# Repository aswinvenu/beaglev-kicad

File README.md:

# BeagleV-Kicad

BeagleV Kicad project files

Convert BeagleV design files from OrCad and Allegro to its equivalent Kicad files.

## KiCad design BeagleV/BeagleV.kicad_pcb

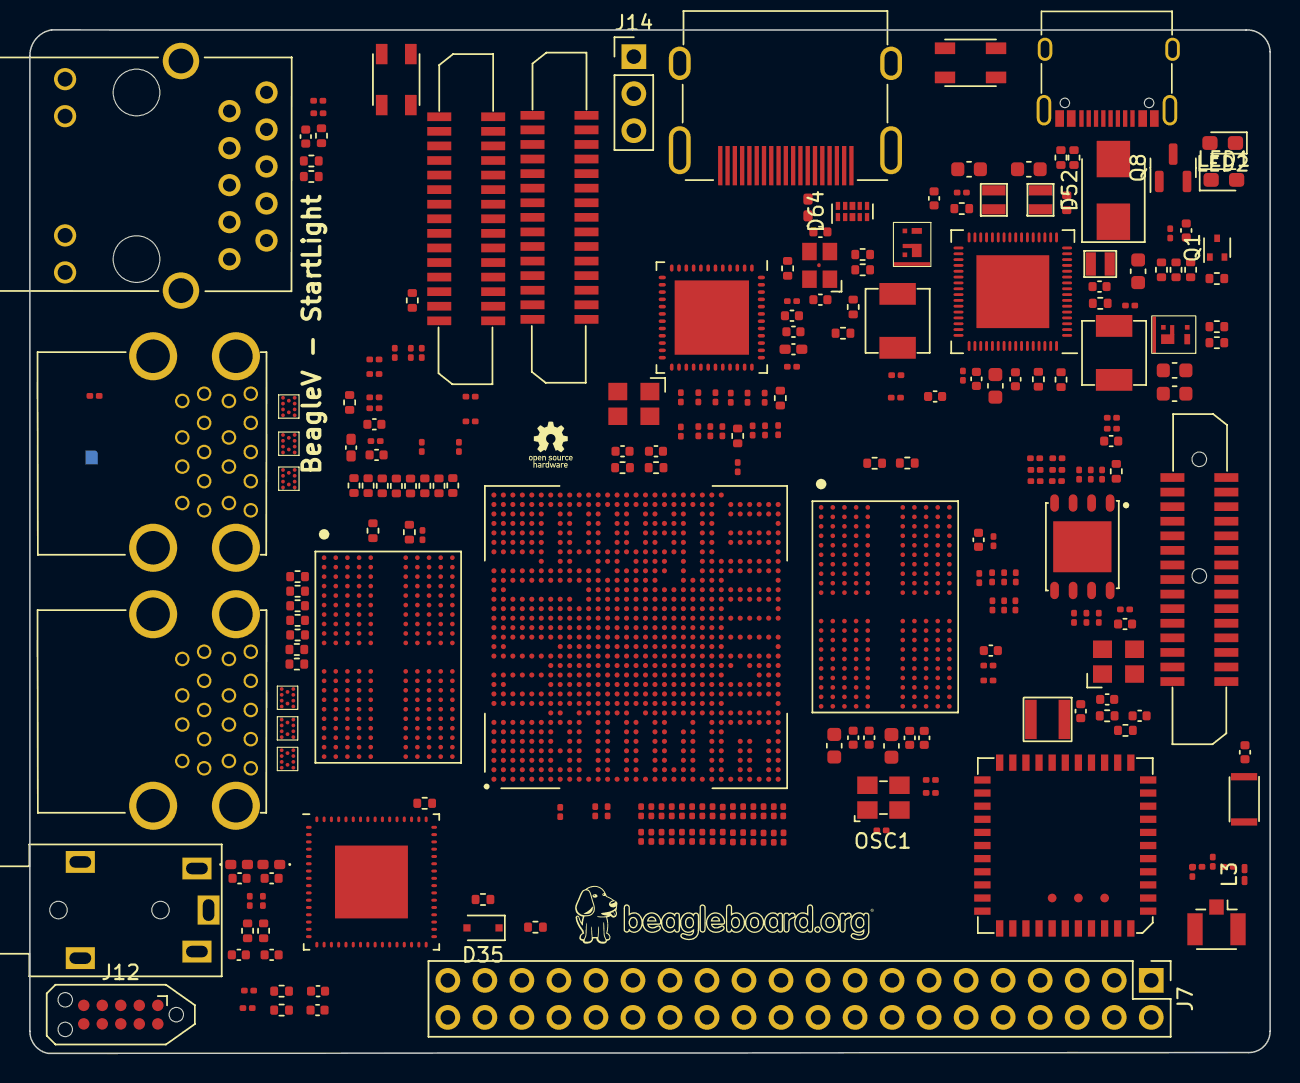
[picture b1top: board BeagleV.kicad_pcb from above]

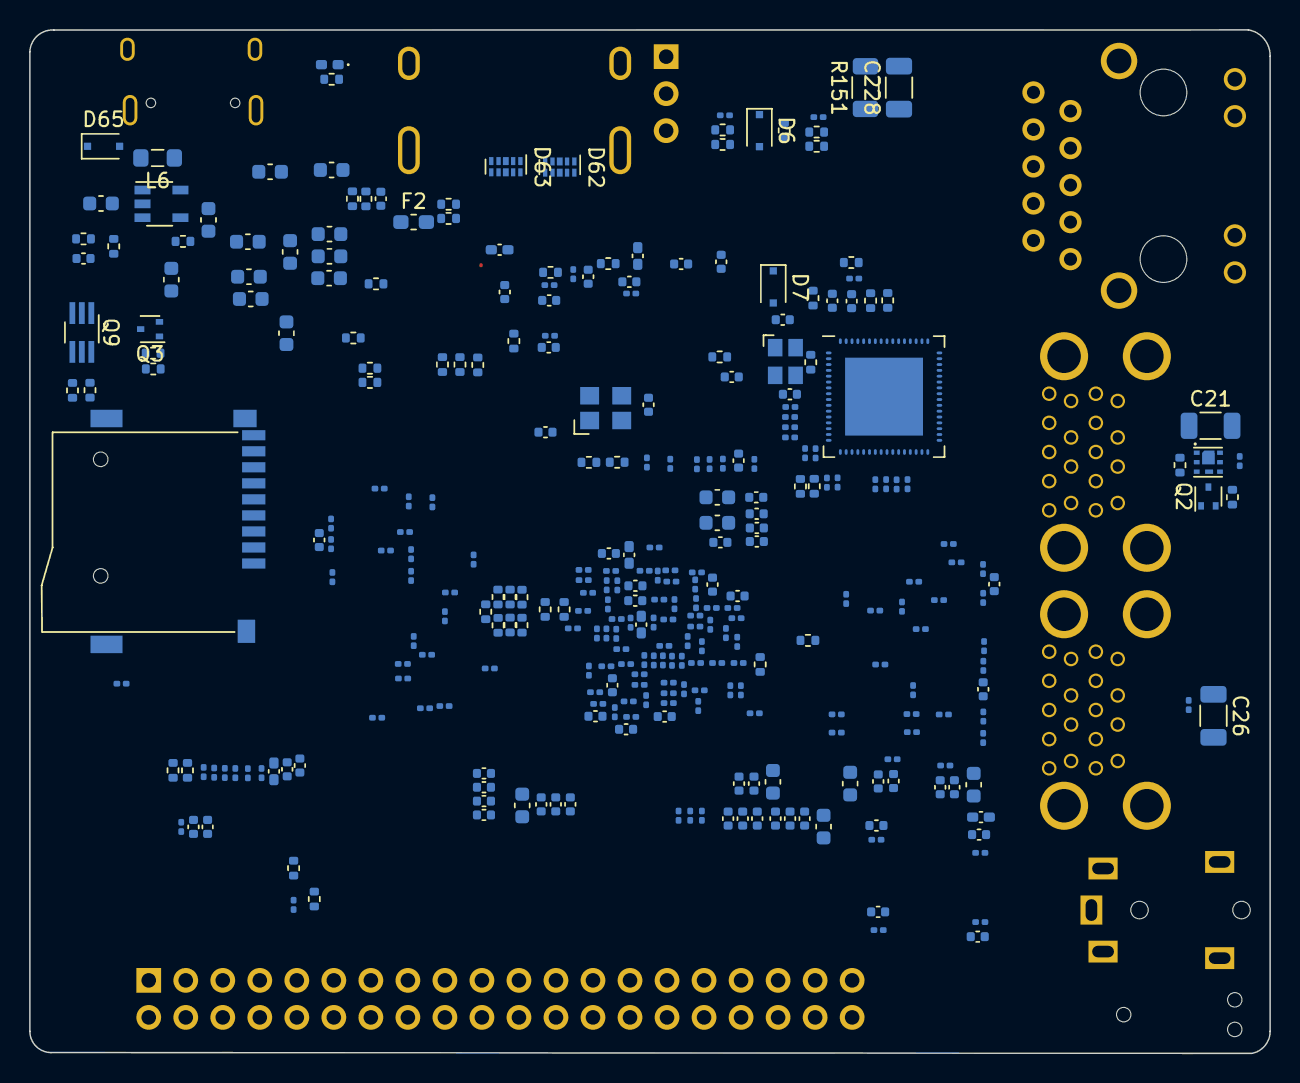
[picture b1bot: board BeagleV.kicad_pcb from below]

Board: 12 copper layers, 85.1 x 70.2 mm, 574 parts (315 on the bottom side), 536 nets.

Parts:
ANT1: RFECA3216060A1T
C1, C5, C6, C7, C8, C9, C11, C12, C13, C14, C15, C16, C17, C18, C19, C20, C24, C25, C29, C33, C35, C37, C39, C50, C51, C52, C53, C54, C55, C56, C57, C58, C61, C62, C63, C64, C65, C66, C70, C71, C72, C73, C74, C75, C76, C77, C78, C82, C83, C84, C85, C86, C87, C88, C89, C90, C93, C94, C95, C96, C97, C98, C102, C103, C104, C105, C106, C107, C108, C109, C110, C112, C113, C114, C115, C117, C118, C119, C124, C125, C126, C127, C128, C129, C130, C131, C132, C137, C138, C139, C140, C146, C147, C148, C149, C150, C151, C152, C153, C154, C161, C162, C163, C164, C165, C166, C167, C168, C169, C170, C171, C172, C173, C174, C175, C179, C180, C181, C183, C184, C185, C186, C189, C190, C191, C193, C194, C195, C199, C201, C203, C205, C207, C209, C210, C211, C212, C217, C219, C221, C229, C237, C238, C239, C240, C241, C242, C243, C244, C245, C267, C269, C270, C272, C277, C279, C281, C282, C286, C287, C297, C300: 100nF/10V; C_0201_0603Metric
C2: 100nF/10V1; C_0201_0603Metric
C3: 100n/10V; C_0201_0603Metric
C4, C10, C22, C23, C28, C32, C34, C36, C38, C91, C92, C99, C111, C177, C230, C231, C232, C278, C280: 10uF/6.3V; C_0402_1005Metric
C21: 100uF/6.3V; C_1206_3216Metric
C26: 100uF/10V; C_1206_3216Metric
C27, C68, C80, C100, C120, C134, C142, C156, C157, C248, C273, C274, C275, C276, C283, C284, C294, C295: 22uF/10V; C_0603_1608Metric
C30, C31: 100uF/4V; C_0402_1005Metric
C40, C227, C311, C312, C313, C314: 10nF/50V; C_0402_1005Metric
C42, C44: DNP; C_0402_1005Metric
C43, C45, C235, C236: 22pF/50V; C_0402_1005Metric
C46, C215, C223, C224: 10pF; C_0402_1005Metric
C47, C233, C250: 100nF/10V; C_0402_1005Metric
C48: 22uF; C_0603_1608Metric
C49, C69, C81, C101, C116, C123, C136, C145, C160, C178, C182, C188, C192, C198, C202, C204, C206, C208, C216, C218, C220, C234, C309, C310: 1uF/10V; C_0402_1005Metric
C59, C60, C67, C187: 10uF/6.4V; C_0402_1005Metric
C79: 10uf/6.4V; C_0402_1005Metric
C121, C122, C135, C143, C158, C159, C288, C298: 10uF/10V; C_0402_1005Metric
C133, C141, C155, C176: 1nF/10V; C_0402_1005Metric
C144: 0uF/10V; C_0402_1005Metric
C196, C226: DNP; C_0201_0603Metric
C197: 100nF; C_0402_1005Metric
C200, C266, C271: 2.2uF/6.3V; C_0402_1005Metric
C213: 1pF/50V; C_0201_0603Metric
C222, C306, C307: 4.7uF/10V; C_0402_1005Metric
C228: 1nF/2kV; C_1206_3216Metric
C246, C247: 22pF; C_0402_1005Metric
C249, C291, C293, C304: 10uF/10V; C_0603_1608Metric
C268, C296: 2.2uF/10V; C_0402_1005Metric
C289, C290, C308: 2.2uF/10V; C_0603_1608Metric
C301: 2.2uF; C_0603_1608Metric
C302: 1nF/50V; C_0402_1005Metric
C303: 10uF; C_0603_1608Metric
C305: 100nF; C_0201_0603Metric
D1, D2, D4: D_TVS; D_0402_1005Metric_Pad0.77x0.64mm_HandSolder
D5: ESDPSA0402V05; D_0402_1005Metric_Pad0.77x0.64mm_HandSolder
D6, D7, D35, D65: PMEG3010CEJ; D_SOD-323F
D27, D28, D29, D30, D31, D32: PCMF2USB3S
D52: SMBJ5.0CA-TR; D_SMB
D62, D63, D64: Protection-Diode; USON-10_2.5x1.0mm_P0.5mm
F2: Fuse; Fuse_0603_1608Metric_Pad1.05x0.95mm_HandSolder
FB1, FB2, FB3, FB6: FerriteBead; L_0402_1005Metric_Pad0.77x0.64mm_HandSolder
FB4, FB7, FB8, FB9: FerriteBead 120R; L_0402_1005Metric_Pad0.77x0.64mm_HandSolder
J1, J2, J9: FPC_CONN_2X15P; FPC-1-1734248-5
J3: audio_5p_mj2135_5d6_14_7x7x6mm; PJ322
J4, J5: USB-TYPE-A-3.0; Stacked-USB-TypeA
J6: LPJG0801HBNL; LPJG0801EBNL
J7: PI-Connector-2x20-2.54mm; PinHeader_2x20_P2.54mm_Vertical
J8: U.FL-R-SMT-1
J10: MICRO_SD_ST_TF_003A_16_1x14_5mm; ST-TF-003A
J11: ST-HD-010; HDMI-Type-A
J12: JTAG-Connector; Tag-Connect_TC2050-IDC-NL_2x05_P1.27mm_Vertical
J13: USB_TYPE_C; USB-Type-C
J14: DNP Conn_01x03_Male; PinHeader_1x03_P2.54mm_Vertical
L1, L7, L8: 1uH; WPN201610H_2x1.6
L2: 3.3uH; Sunlord_3.0x3.0
L3: 10nH; L_0201_0603Metric_Pad0.64x0.40mm_HandSolder
L4: 0.47uH; Codaca_4.4x4.4
L5: 0.56uH; Codaca_4.4x4.4
L6: 10uH; L_0805_2012Metric_Pad1.05x1.20mm_HandSolder
LED1: GREEN LED; LED_0603_1608Metric_Pad1.05x0.95mm_HandSolder
LED2: RED LED; LED_0603_1608Metric_Pad1.05x0.95mm_HandSolder
OSC1: 32.768kHz-clock; 7XZ-32.768KHz
Q1, Q2, Q3: CJ1012; SOT-523
Q6, Q7: CSD87381P
Q8: IRLML6401; SOT-23
Q9: BCM857BS-7F-F; SOT-363_SC-70-6_Handsoldering
R1, R28, R29, R30, R31, R32, R33, R34, R123, R124, R125, R126, R134, R137, R147, R148, R149, R150, R152, R153: 10K; R_0201_0603Metric
R2, R3, R35, R38, R55, R56, R84, R85, R117, R161: 1K; R_0402_1005Metric
R4, R101, R127, R128, R129, R131, R167: 4.7K; R_0402_1005Metric
R5, R6, R7, R8, R9, R10, R11, R12, R13, R14, R15, R16, R17, R18, R19, R20, R21, R22, R41, R42, R43, R44, R45, R46, R47, R48, R49, R50, R51, R52, R53, R54, R87, R88, R89, R90, R91, R92, R93, R94, R102, R103, R104, R105, R106, R107, R108, R109, R110, R113, R114, R145, R156, R157, R158, R232, R233, R234, R235, R236, R237, R238, R265, R266, R267, R268: 33R; R_0201_0603Metric
R23: 680R; R_0402_1005Metric
R24, R86: 27K; R_0402_1005Metric
R25, R26, R144, R146, R160: 100K; R_0402_1005Metric
R27, R37, R58, R59, R63, R67, R76, R116, R119, R121, R122, R140, R155, R165, R166, R254, R255, R257, R259, R260: 0R; R_0402_1005Metric
R36, R39: 1K; R_0201_0603Metric
R57, R115, R120, R143, R263: 1M; R_0402_1005Metric
R60: 12K; R_0402_1005Metric
R61, R65, R66, R69, R70, R74, R75, R78, R79, R95, R96, R97, R98, R136, R139, R154, R164, R240, R242, R244, R247: DNP; R_0402_1005Metric
R62, R71, R72, R80, R81, R184: 240R; R_0402_1005Metric
R64, R68, R73, R77, R82, R83, R99, R100, R111, R112, R118, R138, R142, R241, R243, R245, R246, R252: 10K; R_0402_1005Metric
R130, R135, R141: DNP; R_0201_0603Metric
R133: 0R; R_0201_0603Metric
R151: 1M; R_1206_3216Metric
R159: 10k; R_0402_1005Metric
R162, R163, R261: 49.9K; R_0402_1005Metric
R248, R249: 5.1K; R_0402_1005Metric
R256, R262: 12.1K; R_0402_1005Metric
R258: 2.2K; R_0402_1005Metric
R264: 13.3K; R_0402_1005Metric
R269, R270, R271, R272: 120R; R_0402_1005Metric
SW2, SW3: Tactile-Switch; switch
U1: GL3520-OS322; GL3520-22-QFN-64_EP_8x8_Pitch0.4mm
U2: ETA6020D2G; ETA6020-DFN2x2-6L
U5: KSZ9031RNXCA; KSZ9031RNX-QFN-48_EP_7.3x7.3_Pitch0.5mm
U7, U8: 32Gbit_RAM; LPDDR4-200-WFBGA-10x14.5
U9: VIC-V10; JH7100 - BGA-961_31x31_20.5x20.5mm
U11: TDA19988; TDA19988-QFN-64_EP_9x9_Pitch0.5mm
U12: AP6236
U13: LMR62014; DBV0005A-SOT-23
U14: TPS65086100; TPS650861-QFN-64_EP_8.15x8.15_Pitch0.4mm
U16: GD25LQ256DWIGR; GD25LQ256D
X1: 25MHz; SMCE-2520
X2: 25MHz; SMCE-3225
X3: 27MHz; SMCE-3225
X4: Crystal; SMCE-3225
X6: 25MHz - Crystal; SMCE-2520

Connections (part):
3V3_WIFI: C3.1, C229.1, C230.1, C231.1, C233.1, C234.1, FB9.2, OSC1.1 (EN), OSC1.4 (VDD), R130.1, R137.2, R141.1, U12.9 (VBAT), U12.22 (VDDIO)
+1V1: C48.1, C49.1, C50.1, C51.1, C52.1, C53.1, C54.1, C55.1, C56.1, C57.1, C58.1, C59.1, C68.1, C69.1, C70.1, C71.1, C72.1, C73.1, C74.1, C75.1, C76.1, C77.1, C78.1, C79.1, C80.1, C81.1, C82.1, C83.1, C84.1, C85.1, C86.1, C87.1, C88.1, C89.1, C90.1, C91.1, C100.1, C101.1, C102.1, C103.1, C104.1, C105.1, C106.1, C107.1, C108.1, C109.1, C110.1, C111.1, C120.1, C121.1, C122.1, C123.1, C124.1, C125.1, C126.1, C127.1, C128.1, C129.1, C130.1, C131.1, C132.1, C133.1, C142.1, C143.1, C144.1, C145.1, C146.1, C147.1, C148.1, C149.1, C150.1, C151.1, C152.1, C153.1, C154.1, C155.1, C282.2, C297.2, C298.2, L5.2, R62.1, R64.1, R70.1, R71.1, R72.1, R73.1, R79.1, R82.1, R83.1, R184.1, U8.A4 (VDD2_00), U8.A9 (VDD2_1), U8.AB4 (VDD2_22), U8.AB9 (VDD2_23), U8.F5 (VDD2_2), U8.F8 (VDD2_3), U8.H1 (VDD2_4), U8.H5 (VDD2_5), U8.H8 (VDD2_6), U8.H12 (VDD2_7), U8.K1 (VDD2_8), U8.K3 (VDD2_9), U8.K10 (VDD2_10), U8.K12 (VDD2_11), U8.N1 (VDD2_12)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
+1V2: C10.1, C16.1, C17.1, C18.1, C27.2, C30.1, C248.2, FB2.1, FB3.1, FB4.1, L1.2, R37.1, U1.39 (DVDD12), U1.56 (DVDD12_1), U1.62 (DVDD12_2), U14.22 (FB5)
+1V8: C60.1, C61.1, C62.1, C63.1, C64.1, C65.1, C66.1, C67.1, C92.1, C93.1, C94.1, C95.1, C96.1, C97.1, C98.1, C99.1, C134.1, C135.1, C136.1, C137.1, C138.1, C139.1, C140.1, C141.1, C198.1, C199.1, C202.1, C203.1, C206.1, C207.1, C210.1, C211.1, C212.1, C216.1, C217.1, C275.2, C276.2, C296.2, FB6.2, J12.1, L8.2, R98.1, R99.2, R101.2, R161.1, R240.1, R242.1, R244.1, R246.1, SW3.1, SW3.3, U7.F1 (VDD1_00), U7.F12 (VDD1_1), U7.G4 (VDD1_2), U7.G9 (VDD1_3), U7.T4 (VDD1_4), U7.T9 (VDD1_5), U7.U1 (VDD1_6), U7.U12 (VDD1_7), U8.F1 (VDD1_00), U8.F12 (VDD1_1), U8.G4 (VDD1_2), U8.G9 (VDD1_3), U8.T4 (VDD1_4), U8.T9 (VDD1_5), U8.U1 (VDD1_6), U8.U12 (VDD1_7), U9.AB21 (DVDD18_OTP), U9.AD24 (AVDD18_USB), U9.M8 (VDD18_00), U9.M9 (VDD18_01), U9.M23 (AVDD18_MIPITX), U9.N8 (VDD18_02), U9.N9 (VDD18_03), U9.N10 (VDD18_04), U9.N11 (VDD18_05), U9.P8 (VDD18_06), U9.P9 (VDD18_07), U9.P10 (VDD18_08), U9.P11 (VDD18_09), U9.R8 (VDD18_10), U9.R9 (VDD18_11), U9.R10 (VDD18_12), U9.R11 (VDD18_13), U9.T23 (AVDD18_MIPIRX), U9.W23 (AVDD18_TS), U14.23 (FB4), U14.32 (PVINSWA1), U16.8 (VCC)
+3V3: C1.1, C2.1, C177.1, C178.1, C179.1, C180.1, C181.1, C182.1, C183.1, C184.1, C187.1, C188.1, C189.1, C190.1, C191.1, C192.1, C193.1, C194.1, C195.1, C272.1, C273.2, C274.2, C278.1, C279.1, FB1.1, FB8.1, FB9.1, J1.15, J2.15, J7.1, J7.17, J9.14, J9.15, J10.4 (VDD), L7.2, R1.2, R27.1, R86.1, R100.1, R112.2, R123.2, R124.2, R125.2, R126.2, R127.1, R128.1, R129.1, R131.1, R134.2, R147.2, R160.1, U9.AA9 (VDD3318_SENSOR_00), U9.AA21 (VDD3318_GMII_1), U9.AB9 (VDD3318_SENSOR_1), U9.N13 (VDD3318_CHIPLINK_00), U9.N14 (VDD3318_CHIPLINK_1), U9.R13 (VDD3318_CHIPLINK_2), U9.T13 (VDD3318_CHIPLINK_3), U9.V8 (VDD3318_LCD_00), U9.V9 (VDD3318_LCD_1), U9.W8 (VDD3318_LCD_2), U9.W9 (VDD3318_LCD_3), U9.Y21 (VDD3318_GMII_00), U14.12 (FB3)
+5V: C19.1, C22.1, C249.2, C280.1, C281.1, C283.2, C284.2, C289.2, C290.2, C291.2, C293.2, C294.2, C295.2, C303.1, C308.2, F2.1, J7.2, J7.4, L6.1, Q6.2, Q7.2, Q8.2 (S), Q9.4, R138.2, R263.1, U1.64 (V5), U2.6 (IN), U13.5 (VIN), U14.8 (DRV5V_2_A1), U14.11 (PVIN3), U14.21 (PVIN5), U14.24 (PVIN4), U14.38 (DRV5V_1_6), U14.57 (V5ANA)
/BeagleV 10/100/1000 ETHERNET/GBE1_LED_ACT: J6.13 (YEL-), R30.1, U5.17 (LED1/PME_N1)
/BeagleV 10/100/1000 ETHERNET/GBE1_LED_LINK: J6.12 (GRL-), R29.1, U5.15 (LED2)
/BeagleV 10/100/1000 ETHERNET/GBE1_TRN0: J6.2 (TD1-), U5.3 (TXRXM_P)
/BeagleV 10/100/1000 ETHERNET/GBE1_TRN1: J6.4 (TD2-), U5.6 (TXRXM_B)
/BeagleV 10/100/1000 ETHERNET/GBE1_TRN2: J6.8 (TD3-), U5.8 (TXRXM_C)
/BeagleV 10/100/1000 ETHERNET/GBE1_TRN3: J6.10 (TD4-), U5.11 (TXRXM_D)
/BeagleV 10/100/1000 ETHERNET/GBE1_TRP0: J6.1 (TD1+), U5.2 (TXRXP_P)
/BeagleV 10/100/1000 ETHERNET/GBE1_TRP1: J6.3 (TD2+), U5.5 (TXRXP_B)
/BeagleV 10/100/1000 ETHERNET/GBE1_TRP2: J6.7 (TD3+), U5.7 (TXRXP_C)
/BeagleV 10/100/1000 ETHERNET/GBE1_TRP3: J6.9 (TD4+), U5.10 (TXRXP_D)
/BeagleV 10/100/1000 ETHERNET/LED_MODE: R39.1, U5.41 (CLK125_NDO)
/BeagleV HighIF & Ctrl Other/ATEMP_TEST0: R95.1, U9.U25 (ANA18_TEMP_TEST0)
/BeagleV HighIF & Ctrl Other/ATEMP_TEST1: R96.1, U9.U24 (ANA18_TEMP_TEST1)
/BeagleV HighIF & Ctrl Other/ATEMP_VCAL: C196.2, U9.V25 (ANA18_TEMP_VCAL)
/BeagleV HighIF & Ctrl Other/ATEMP_VSS: R97.2, U9.V24 (ANA18_TEMP_VSS)
/BeagleV HighIF & Ctrl Other/CLK_25M_IN: R115.1, R116.1, U9.Y30 (OSC0_XIN)
/BeagleV HighIF & Ctrl Other/CLK_25M_OUT: C215.1, R115.2, U9.Y31 (OSC0_XOUT), X2.3
/BeagleV HighIF & Ctrl Other/CLK_27M_IN: R120.1, R122.1, U9.V30 (OSC1_XIN)
/BeagleV HighIF & Ctrl Other/CLK_27M_OUT: C224.1, R120.2, U9.V31 (OSC1_XOUT), X3.3
/BeagleV LPDDR (A)/DDR0_ODT1: R68.2, R69.1, R70.2
/BeagleV LPDDR (A)/DDR0_ODT_0: R64.2, R65.2, R66.2, R67.2
/BeagleV LPDDR (A)/DDR0_ODT_1: R67.1, R69.2, U7.G2 (ODT_CA_A1), U7.T2 (ODT_CA_B1)
/BeagleV LPDDR (B)/DDR1_ODT1: R77.2, R78.1, R79.2
/BeagleV LPDDR (B)/DDR1_ODT_0: R76.2, U8.G2 (ODT_CA_A1)
/BeagleV LPDDR (B)/DDR1_ODT_1: R76.1, R78.2, U8.T2 (ODT_CA_B1)
/BeagleV PMIC/CTL5: D5.2 (A2), R118.2, SW2.2, SW2.4, U14.63 (CTL5)
/BeagleV PMIC/PWR_EN: R117.2, U14.13 (CTL1)
/BeagleV VIC LCD & GMI & GPIOs/BOOT_MODE: R246.2, R247.1, U9.M28 (GPIO63/BOOT_MODE)
/BeagleV VIC LCD & GMI & GPIOs/BOOT_SEL0: R240.2, R241.1, U9.E31 (GPIO60/BOOT_SEL0)
/BeagleV VIC LCD & GMI & GPIOs/BOOT_SEL1: R242.2, R243.1, U9.F31 (GPIO61/BOOT_SEL1)
/BeagleV W iFi, Bluetooth/26M_XTAL_IN: C235.1, R154.1, U12.10 (XTAL_IN), X4.3
/BeagleV W iFi, Bluetooth/26M_XTAL_OUT: R154.2, R155.2, U12.11 (XTAL_OUT)
/BeagleV W iFi, Bluetooth/LPO_32K: R114.2, R137.1, U12.24 (LPO)
/BeagleVUSB 3.0 HUB/V33: C4.1, C5.1, C6.1, C7.1, C8.1, C9.1, R25.2, R26.2, R144.2, R146.2, U1.38 (VBUS), U1.40 (DVDD), U1.45 (AVDD), U1.48 (AVDD1), U1.51 (AVDD2), U1.54 (DVDD1), U1.63 (V33)
AVDD3V3_USB: C208.1, C209.1, FB8.2, U9.AA23 (AVDD33_USB)
AVDD09_PLL: C116.1, C117.1, C118.1, C119.1, FB7.1, U9.U21 (AVDD09_PLL0), U9.U22 (AVDD09_PLL1), U9.V21 (AVDD09_PLL2)
BOOT_SEL2: R244.2, R245.1, SW3.2, SW3.4, U9.F30 (GPIO62/BOOT_SEL2)
CDTX_DSI_CN: J9.5, U9.J30 (CDTX_L2N)
CDTX_DSI_CP: J9.6, U9.J31 (CDTX_L2P)
CDTX_DSI_DN0: J9.8, U9.G30 (CDTX_L0N)
CDTX_DSI_DN1: J9.2, U9.H30 (CDTX_L1N)
CDTX_DSI_DP0: J9.9, U9.G31 (CDTX_L0P)
CDTX_DSI_DP1: J9.3, U9.H31 (CDTX_L1P)
CSI1RX_CLK_N: J2.8, U9.M30 (CSI2RX_DN5)
CSI1RX_CLK_P: J2.9, U9.M31 (CSI2RX_DP5)
CSI1RX_DN0: J2.2, U9.P31 (CSI2RX_DP3)
CSI1RX_DN1: J2.5, U9.N30 (CSI2RX_DN4)
CSI1RX_DP0: J2.3, U9.P30 (CSI2RX_DN3)
CSI1RX_DP1: J2.6, U9.N31 (CSI2RX_DP4)
CSI2RX_CLK_N: J1.8, U9.U30 (CSI2RX_DN0)
CSI2RX_CLK_P: J1.9, U9.U31 (CSI2RX_DP0)
CSI2RX_DN0: J1.2, U9.T30 (CSI2RX_DN1)
CSI2RX_DN1: J1.5, U9.R30 (CSI2RX_DN2)
CSI2RX_DP0: J1.3, U9.T31 (CSI2RX_DP1)
CSI2RX_DP1: J1.6, U9.R31 (CSI2RX_DP2)
DDR0_A0: U7.H2 (CA0_A), U7.R2 (CA0_B)
DDR0_A1: U7.J2 (CA1_A), U7.P2 (CA1_B)
DDR0_A2: U7.H9 (CA2_A), U7.R9 (CA2_B)
DDR0_A3: U7.H10 (CA3_A), U7.R10 (CA3_B)
DDR0_A4: U7.H11 (CA4_A), U7.R11 (CA4_B)
DDR0_A5: U7.J11 (CA5_A), U7.P11 (CA5_B)
DDR0_CKE0: U7.J4 (CKE0_A), U7.P4 (CKE0_B)
DDR0_CKE1: U7.J5 (CKE1_A), U7.P5 (CKE1_B)
DDR0_CLK0N: U7.J9 (CK_C_A), U7.P9 (CK_C_B)
DDR0_CLK0P: U7.J8 (CK_T_A), U7.P8 (CK_T_B)
DDR0_CS0: U7.H4 (CS0_A), U7.R4 (CS0_B)
DDR0_CS1: U7.H3 (CS1_A), U7.R3 (CS1_B)
DDR0_DQ0: U7.B2 (DQ0_A), U9.F23 (DDR0_DQ00)
DDR0_DQ1: U7.C2 (DQ1_A), U9.E23 (DDR0_DQ1)
DDR0_DQ2: U7.E2 (DQ2_A), U9.D22 (DDR0_DQ2)
DDR0_DQ3: U7.F2 (DQ3_A), U9.F22 (DDR0_DQ3)
DDR0_DQ4: U7.F4 (DQ4_A), U9.C22 (DDR0_DQ4)
DDR0_DQ5: U7.E4 (DQ5_A), U9.B22 (DDR0_DQ5)
DDR0_DQ6: U7.C4 (DQ6_A), U9.A23 (DDR0_DQ6)
DDR0_DQ7: U7.B4 (DQ7_A), U9.A22 (DDR0_DQ7)
DDR0_DQ8: U7.B11 (DQ8_A), U9.A21 (DDR0_DQ8)
DDR0_DQ9: U7.C11 (DQ9_A), U9.C20 (DDR0_DQ9)
DDR0_DQ10: U7.E11 (DQ10_A), U9.E20 (DDR0_DQ10)
DDR0_DQ11: U7.F11 (DQ11_A), U9.D20 (DDR0_DQ11)
DDR0_DQ12: U7.F9 (DQ12_A), U9.E19 (DDR0_DQ12)
DDR0_DQ13: U7.E9 (DQ13_A), U9.D19 (DDR0_DQ13)
DDR0_DQ14: U7.C9 (DQ14_A), U9.B19 (DDR0_DQ14)
DDR0_DQ15: U7.B9 (DQ15_A), U9.A19 (DDR0_DQ15)
DDR0_DQ16: U7.AA2 (DQ0_B), U9.A5 (DDR0_DQ16)
DDR0_DQ17: U7.Y2 (DQ1_B), U9.D7 (DDR0_DQ17)
DDR0_DQ18: U7.V2 (DQ2_B), U9.C7 (DDR0_DQ18)
DDR0_DQ19: U7.U2 (DQ3_B), U9.E7 (DDR0_DQ19)
DDR0_DQ20: U7.U4 (DQ4_B), U9.B5 (DDR0_DQ20)
DDR0_DQ21: U7.V4 (DQ5_B), U9.C6 (DDR0_DQ21)
DDR0_DQ22: U7.Y4 (DQ6_B), U9.E6 (DDR0_DQ22)
DDR0_DQ23: U7.AA4 (DQ7_B), U9.B4 (DDR0_DQ23)
DDR0_DQ24: U7.AA11 (DQ8_B), U9.A2 (DDR0_DQ24)
DDR0_DQ25: U7.Y11 (DQ9_B), U9.B3 (DDR0_DQ25)
DDR0_DQ26: U7.V11 (DQ10_B), U9.A3 (DDR0_DQ26)
DDR0_DQ27: U7.U11 (DQ11_B), U9.C4 (DDR0_DQ27)
DDR0_DQ28: U7.U9 (DQ12_B), U9.B2 (DDR0_DQ28)
DDR0_DQ29: U7.V9 (DQ13_B), U9.B1 (DDR0_DQ29)
DDR0_DQ30: U7.Y9 (DQ14_B), U9.A1 (DDR0_DQ30)
DDR0_DQ31: U7.AA9 (DQ15_B), U9.C2 (DDR0_DQ31)
DDR1_A0: U8.H2 (CA0_A), U8.R2 (CA0_B), U9.AG16 (DDR1_ADR00), U9.C10 (DDR0_ADR00)
DDR1_A1: U8.J2 (CA1_A), U8.P2 (CA1_B), U9.AJ18 (DDR1_ADR1), U9.B10 (DDR0_ADR1)
DDR1_A2: U8.H9 (CA2_A), U8.R9 (CA2_B), U9.A15 (DDR0_ADR2), U9.AJ16 (DDR1_ADR2)
DDR1_A3: U8.H10 (CA3_A), U8.R10 (CA3_B), U9.AF14 (DDR1_ADR3), U9.D10 (DDR0_ADR3)
DDR1_A4: U8.H11 (CA4_A), U8.R11 (CA4_B), U9.AL14 (DDR1_ADR4), U9.D12 (DDR0_ADR4)
DDR1_A5: U8.J11 (CA5_A), U8.P11 (CA5_B), U9.AG14 (DDR1_ADR5), U9.E10 (DDR0_ADR5)
DDR1_CKE0: U8.J4 (CKE0_A), U8.P4 (CKE0_B), U9.AG23 (DDR1_CKE0), U9.AJ24 (DDR1_CKE1), U9.C17 (DDR0_CKE0), U9.F17 (DDR0_CKE1)
DDR1_CKE1: U8.J5 (CKE1_A), U8.P5 (CKE1_B)
DDR1_CLK0N: U8.J9 (CK_C_A), U8.P9 (CK_C_B), U9.AK18 (DDR1_CK_N0), U9.B14 (DDR0_CK_N0)
DDR1_CLK0P: U8.J8 (CK_T_A), U8.P8 (CK_T_B), U9.A14 (DDR0_CK_P0), U9.AL18 (DDR1_CK_P0)
DDR1_CLK1N: U9.AK16 (DDR1_CK_N1), U9.B12 (DDR0_CK_N1)
DDR1_CLK1P: U9.A12 (DDR0_CK_P1), U9.AL16 (DDR1_CK_P1)
DDR1_CS0: U8.H4 (CS0_A), U8.R4 (CS0_B), U9.AK23 (DDR1_CS_N0), U9.F19 (DDR0_CS_N0)
DDR1_CS1: U8.H3 (CS1_A), U8.R3 (CS1_B), U9.A17 (DDR0_CS_N1), U9.AH21 (DDR1_CS_N1)
DDR1_CS2: U9.AH20 (DDR1_CS_N2), U9.B17 (DDR0_CS_N2)
DDR1_CS3: U9.AF20 (DDR1_CS_N3), U9.E14 (DDR0_CS_N3)
DDR1_DMI0: U8.C3 (DMIO_A), U9.AG30 (DDR1_DM_DBI_N0), U9.E22 (DDR0_DM_DBI_N0)
DDR1_DMI1: U8.C10 (DMI1_A), U9.AJ26 (DDR1_DM_DBI_N1), U9.C19 (DDR0_DM_DBI_N1)
DDR1_DMI2: U8.Y3 (DMIO_B), U9.AG11 (DDR1_DM_DBI_N2), U9.D6 (DDR0_DM_DBI_N2)
DDR1_DMI3: U8.Y10 (DMI1_B), U9.AH8 (DDR1_DM_DBI_N3), U9.D4 (DDR0_DM_DBI_N3)
DDR1_DQ0: U8.B2 (DQ0_A), U9.AF29 (DDR1_DQ00)
DDR1_DQ1: U8.C2 (DQ1_A), U9.AG29 (DDR1_DQ1)
DDR1_DQ2: U8.E2 (DQ2_A), U9.AH30 (DDR1_DQ2)
DDR1_DQ3: U8.F2 (DQ3_A), U9.AF30 (DDR1_DQ3)
DDR1_DQ4: U8.F4 (DQ4_A), U9.AJ29 (DDR1_DQ4)
DDR1_DQ5: U8.E4 (DQ5_A), U9.AK29 (DDR1_DQ5)
DDR1_DQ6: U8.C4 (DQ6_A), U9.AL30 (DDR1_DQ6)
DDR1_DQ7: U8.B4 (DQ7_A), U9.AL29 (DDR1_DQ7)
DDR1_DQ8: U8.B11 (DQ8_A), U9.AF26 (DDR1_DQ8)
DDR1_DQ9: U8.C11 (DQ9_A), U9.AH27 (DDR1_DQ9)
DDR1_DQ10: U8.E11 (DQ10_A), U9.AG27 (DDR1_DQ10)
DDR1_DQ11: U8.F11 (DQ11_A), U9.AG26 (DDR1_DQ11)
DDR1_DQ12: U8.F9 (DQ12_A), U9.AL27 (DDR1_DQ12)
DDR1_DQ13: U8.E9 (DQ13_A), U9.AL26 (DDR1_DQ13)
DDR1_DQ14: U8.C9 (DQ14_A), U9.AF24 (DDR1_DQ14)
DDR1_DQ15: U8.B9 (DQ15_A), U9.AF23 (DDR1_DQ15)
DDR1_DQ16: U8.AA2 (DQ0_B), U9.AL11 (DDR1_DQ16)
DDR1_DQ17: U8.Y2 (DQ1_B), U9.AK11 (DDR1_DQ17)
DDR1_DQ18: U8.V2 (DQ2_B), U9.AL10 (DDR1_DQ18)
DDR1_DQ19: U8.U2 (DQ3_B), U9.AJ11 (DDR1_DQ19)
DDR1_DQ20: U8.U4 (DQ4_B), U9.AG10 (DDR1_DQ20)
DDR1_DQ21: U8.V4 (DQ5_B), U9.AH11 (DDR1_DQ21)
DDR1_DQ22: U8.Y4 (DQ6_B), U9.AF11 (DDR1_DQ22)
DDR1_DQ23: U8.AA4 (DQ7_B), U9.AF10 (DDR1_DQ23)
DDR1_DQ24: U8.AA11 (DQ8_B), U9.AL8 (DDR1_DQ24)
DDR1_DQ25: U8.Y11 (DQ9_B), U9.AL7 (DDR1_DQ25)
DDR1_DQ26: U8.V11 (DQ10_B), U9.AK8 (DDR1_DQ26)
DDR1_DQ27: U8.U11 (DQ11_B), U9.AJ8 (DDR1_DQ27)
DDR1_DQ28: U8.U9 (DQ12_B), U9.AF8 (DDR1_DQ28)
DDR1_DQ29: U8.V9 (DQ13_B), U9.AG8 (DDR1_DQ29)
DDR1_DQ30: U8.Y9 (DQ14_B), U9.AG7 (DDR1_DQ30)
DDR1_DQ31: U8.AA9 (DQ15_B), U9.AF7 (DDR1_DQ31)
DDR1_DQS0N: U8.E3 (DQS0_C_A), U9.AJ30 (DDR1_DQS_N0), U9.C23 (DDR0_DQS_N0)
DDR1_DQS0P: U8.D3 (DQS0_T_A), U9.AK30 (DDR1_DQS_P0), U9.B23 (DDR0_DQS_P0)
DDR1_DQS1N: U8.E10 (DQS1_C_A), U9.A20 (DDR0_DQS_N1), U9.AK27 (DDR1_DQS_N1)
DDR1_DQS1P: U8.D10 (DQS1_T_A), U9.AJ27 (DDR1_DQS_P1), U9.B20 (DDR0_DQS_P1)
DDR1_DQS2N: U8.V3 (DQS0_C_B), U9.AJ10 (DDR1_DQS_N2), U9.B6 (DDR0_DQS_N2)
DDR1_DQS2P: U8.W3 (DQS0_T_B), U9.A6 (DDR0_DQS_P2), U9.AK10 (DDR1_DQS_P2)
DDR1_DQS3N: U8.V10 (DQS1_C_B), U9.AK7 (DDR1_DQS_N3), U9.C3 (DDR0_DQS_N3)
DDR1_DQS3P: U8.W10 (DQS1_T_B), U9.AJ7 (DDR1_DQS_P3), U9.D3 (DDR0_DQS_P3)
DDR1_ODT0: U9.AH24 (DDR1_ODT0), U9.D17 (DDR0_ODT0)
DDR1_ODT1: U9.AH23 (DDR1_ODT1), U9.G17 (DDR0_ODT1)
DDR1_RSTN: U8.T11 (RESET_N), U9.AL23 (DDR1_RESET_N), U9.B18 (DDR0_RESET_N)
Earth: C228.2, J4.19 (TAB), J4.20 (TAB), J4.21 (TAB), J4.22 (TAB), J5.19 (TAB), J5.20 (TAB), J5.21 (TAB), J5.22 (TAB), J6.15 (GND1), J6.16 (GND2), J10.12 (G3), J10.13 (G4), J11.20, J11.21, J11.22, J11.23, J13.S1, J13.S2, J13.S3, J13.S4, R151.2
FNSH115_GMAC_GTXCLK: R41.1, U9.AA27 (FUNC_SHARE115/GMAC_PHY_GTXCLK)
FNSH117_GMAC_TXEN: R42.1, U9.AB30 (FUNC_SHARE117/GMAC_PHY_TXEN)
FNSH119_GMAC_TXD0: R43.1, U9.AB31 (FUNC_SHARE119/GMAC_PHY_TXD0)
FNSH119_GMAC_TXD1: R44.1, U9.AA26 (FUNC_SHARE120/GMAC_PHY_TXD1)
FNSH119_GMAC_TXD2: R45.1, U9.AA25 (FUNC_SHARE121/GMAC_PHY_TXD2)
FNSH119_GMAC_TXD3: R46.1, U9.V29 (FUNC_SHARE122/GMAC_PHY_TXD3)
FNSH127_GMAC_RXCLK: R47.1, U9.V27 (FUNC_SHARE127/GMAC_PHY_RXCLK)
FNSH128_GMAC_RXDV: R48.1, U9.AA31 (FUNC_SHARE128/GMAC_PHY_RXDV)
FNSH130_GMAC_RXD0: R49.1, U9.P28 (FUNC_SHARE130/GMAC_PHY_RXD0)
FNSH130_GMAC_RXD1: R50.1, U9.V28 (FUNC_SHARE131/GMAC_PHY_RXD1)
FNSH130_GMAC_RXD2: R51.1, U9.U28 (FUNC_SHARE132/GMAC_PHY_RXD2)
FNSH130_GMAC_RXD3: R52.1, U9.V26 (FUNC_SHARE133/GMAC_PHY_RXD3)
FNSH140_GMAC_MDC: R53.1, U9.R28 (FUNC_SHARE140/GMAC_MDC)
FNSH141_GMAC_MDIO: R54.1, U9.Y29 (FUNC_SHARE141/GMAC_MDIO)
GND: ANT1.2, C1.2, C2.2, C3.2, C4.2, C5.2, C6.2, C7.2, C8.2, C9.2, C10.2, C11.2, C12.2, C13.2, C14.2, C15.2, C16.2, C17.2, C18.2, C19.2, C20.2, C21.2, C22.2, C23.2, C25.2, C26.2, C27.1, C28.2, C29.2, C30.2, C31.2, C32.2, C33.2, C34.2, C35.2, C36.2, C37.2, C38.2, C39.2, C40.2, C42.2, C43.1, C44.1, C45.1, C46.2, C47.2, C48.2, C49.2, C50.2, C51.2, C52.2, C53.2, C54.2, C55.2, C56.2, C57.2, C58.2, C59.2, C60.2, C61.2, C62.2, C63.2, C64.2, C65.2, C66.2, C67.2, C68.2, C69.2, C70.2, C71.2, C72.2, C73.2, C74.2, C75.2, C76.2, C77.2, C78.2, C79.2, C80.2, C81.2, C82.2, C83.2, C84.2, C85.2, C86.2, C87.2, C88.2, C89.2, C90.2, C91.2, C92.2, C93.2, C94.2, C95.2, C96.2, C97.2, C98.2, C99.2, C100.2, C101.2, C102.2, C103.2, C104.2, C105.2, C106.2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
GPIO0: J7.40, U9.E1 (FUNC_SHARE000/X2C_TX_CLK)
GPIO1: J7.37, U9.D1 (FUNC_SHARE001/X2C_TX_RST)
GPIO2: J7.38, U9.F2 (FUNC_SHARE002/X2C_TX_SEND)
GPIO3: J7.35, U9.G2 (FUNC_SHARE003/X2C_TX_DATA0)
GPIO4: J7.36, U9.G6 (FUNC_SHARE004/X2C_TX_DATA1)
GPIO5: J7.33, U9.F6 (FUNC_SHARE005/X2C_TX_DATA2)
GPIO6: J7.31, U9.F1 (FUNC_SHARE006/X2C_TX_DATA3)
GPIO7: J7.32, U9.G1 (FUNC_SHARE007/X2C_TX_DATA4)
GPIO8: J7.29, U9.J7 (FUNC_SHARE008/X2C_TX_DATA5)
GPIO9: J7.27, U9.G5 (FUNC_SHARE009/X2C_TX_DATA6)
GPIO10: J7.28, U9.H2 (FUNC_SHARE010/X2C_TX_DATA7)
GPIO11: J7.26, U9.H1 (FUNC_SHARE011/X2C_TX_DATA8)
GPIO12: J7.23, U9.F5 (FUNC_SHARE012/X2C_TX_DATA9)
GPIO13: J7.10, R160.2, U9.K7 (FUNC_SHARE013/X2C_TX_DATA10)
GPIO14: J7.8, U9.J4 (FUNC_SHARE014/X2C_TX_DATA11)
GPIO15: J7.24, U9.J3 (FUNC_SHARE015/X2C_TX_DATA12)
GPIO16: J7.21, U9.J6 (FUNC_SHARE016/X2C_TX_DATA13)
GPIO17: J7.22, U9.F4 (FUNC_SHARE017/X2C_TX_DATA14)
GPIO18: J7.19, U9.J2 (FUNC_SHARE018/X2C_TX_DATA15)
GPIO19: J7.18, U9.K4 (FUNC_SHARE019/X2C_TX_DATA16)
GPIO20: J7.15, U9.G4 (FUNC_SHARE020/X2C_TX_DATA17)
GPIO21: J7.16, U9.K6 (FUNC_SHARE021/X2C_TX_DATA18)
GPIO22: J7.13, U9.J1 (FUNC_SHARE022/X2C_TX_DATA19)
GPIO23_DAC_PW ML: C309.1, U9.K2 (FUNC_SHARE023/X2C_TX_DATA20)
GPIO24_DAC_PW MR: C310.1, U9.J5 (FUNC_SHARE024/X2C_TX_DATA21)
GPIO25_HDMI_12MHZ: R110.1, U11.27 (OSC_IN)
GPIO26_HDMI_BCLK: R113.1, U11.23 (ACLK)
GPIO27_HDMI_I2S_LRCLK: R156.1, U11.24 (AP0)
GPIO28_HDMI_I2S_TX0: R157.1, U11.25 (AP1)
GPIO29_WIFI_SDIO1_CMD: R150.2, U9.M7 (FUNC_SHARE029/X2C_TX_DATA26), U12.16 (SDIO_DATA_CMD)
GPIO30_WIFI_SDIO1_D1: R153.2, U9.M4 (FUNC_SHARE030/X2C_TX_DATA27), U12.19 (SDIO_DATA_1)
GPIO31_WIFI_SDIO1_D3: R149.2, U9.M3 (FUNC_SHARE031/X2C_TX_DATA28), U12.15 (SDIO_DATA_3)
GPIO32_HDMI_INT: R112.1, R158.1, U11.50 (INT)
GPIO33_WIFI_SDIO1_CLK: R145.1, U9.N7 (FUNC_SHARE033/X2C_TX_DATA30)
GPIO34_WIFI_SDIO1_D2: R148.2, U9.M2 (FUNC_SHARE034/X2C_TX_DATA31), U12.14 (SDIO_DATA_2)
GPIO35_BT_RSTN: R130.2, U9.M1 (FUNC_SHARE000/X2C_RX_CLK), U12.34 (BT_RST_M)
GPIO36_WIFI_SDIO1_D0: R152.2, U9.N6 (FUNC_SHARE001/X2C_RX_RST), U12.18 (SDIO_DATA_0)
GPIO37_WIFI_EN: R140.1, U9.N5 (FUNC_SHARE002/X2C_RX_SEND)
GPIO39_BT_UART_CTS: U9.N4 (FUNC_SHARE039/X2C_RX_DATA1), U12.41 (UART_RTS_N)
GPIO40_BT_UART_RXD: U9.R7 (FUNC_SHARE040/X2C_RX_DATA2), U12.42 (UART_TXD)
GPIO41_BT_UART_TXD: U9.R6 (FUNC_SHARE041/X2C_RX_DATA3), U12.43 (UART_RXD)
GPIO42_BT_UART_RTS: U9.P1 (FUNC_SHARE042/X2C_RX_DATA4), U12.44 (UART_CTS_N)
GPIO43_LED: R4.1, U9.N1 (FUNC_SHARE043/X2C_RX_DATA5)
GPIO44: J7.11, U9.R5 (FUNC_SHARE044/X2C_RX_DATA6)
GPIO45: J7.12, U9.R4 (FUNC_SHARE045/X2C_RX_DATA7)
GPIO46: J7.7, U9.R3 (FUNC_SHARE046/X2C_RX_DATA8)
GPIO47: J7.5, U9.R2 (FUNC_SHARE047/X2C_RX_DATA9)
GPIO48: J7.3, U9.T7 (FUNC_SHARE048/X2C_RX_DATA10)
GPIO49_SD_SDIO0_D0: R234.1, U9.T6 (FUNC_SHARE049/X2C_RX_DATA11)
GPIO50_SD_SDIO0_D1: R233.1, U9.R1 (FUNC_SHARE050/X2C_RX_DATA12)
GPIO51_SD_SDIO0_D2: R238.1, U9.T1 (FUNC_SHARE051/X2C_RX_DATA13)
GPIO52_SD_SDIO0_D3: R237.1, U9.T2 (FUNC_SHARE052/X2C_RX_DATA14)
GPIO53_SD_SDIO0_CMD: R236.1, U9.T5 (FUNC_SHARE053/X2C_RX_DATA15)
GPIO54_SD_SDIO0_CLK: R235.1, U9.U1 (FUNC_SHARE054/X2C_RX_DATA16)
GPIO55_GMAC_RESETN: R232.1, U9.T4 (FUNC_SHARE055/X2C_RX_DATA17)
GPIO56_VDD2PEN: R142.2, U9.V1 (FUNC_SHARE056/X2C_RX_DATA18), U14.60 (CTL2)
GPIO57_CSI1_PW DN: J2.11, U9.V2 (FUNC_SHARE057/X2C_RX_DATA19)
GPIO58_CSI0_PW DN: J1.11, U9.V6 (FUNC_SHARE058/X2C_RX_DATA20)
GPIO59_I2C2_SDA: J2.14, J9.13, R127.2, U9.V5 (FUNC_SHARE059/X2C_RX_DATA21)
GPIO60_I2C2_SCL: J2.13, J9.11, R128.2, U9.V3 (FUNC_SHARE060/X2C_RX_DATA22)
GPIO61_I2C0_SDA: J1.14, R121.2, R129.2, U9.V4 (FUNC_SHARE061/X2C_RX_DATA23), U11.51 (CSDA)
GPIO62_I2C0_SCL: J1.13, R119.2, R131.2, U9.W5 (FUNC_SHARE062/X2C_RX_DATA24), U11.52 (CSCL)
GPIO63_GMAC_RESETN: R164.1, U9.V7 (FUNC_SHARE063/X2C_RX_DATA25)
HDMI_1V8: C200.1, C201.1, C266.1, C267.1, C268.1, C269.1, C270.1, C271.1, U11.5 (VDDDC0(1.8V)), U11.29 (VDDDC1(1.8V)), U11.35 (VDDA0(1.8V)), U11.36 (VDDA1(TX)(1.8V)), U11.41 (VDDA2(TX)(1.8V)), U11.46 (VDDA3(TX)(1.8V)), U11.47 (VDDA(PLL0)(1.8V)), U11.48 (VDDA(PLL1)(1.8V))
HUB1_DM: D27.C4, U1.43 (DM1)
HUB1_DP: D27.C3, U1.44 (DP1)
HUB1_SSRX_N: D28.C3, U1.14 (RXN_DS1)
HUB1_SSRX_P: D28.C4, U1.15 (RXP_DS1)
HUB1_SSTX_N: C185.2, D29.C1
HUB1_SSTX_P: C24.2, D29.C2
HUB2_DM: D27.C2, U1.46 (DM2)
HUB2_DP: D27.C1, U1.47 (DP2)
HUB2_SSRX_N: D28.C1, U1.20 (RXN_DS2)
HUB2_SSRX_P: D28.C2, U1.21 (RXP_DS2)
HUB2_SSTX_N: C237.2, D29.C3
HUB2_SSTX_P: C186.2, D29.C4
HUB3_DM: D30.C4, U1.49 (DM3)
HUB3_DP: D30.C3, U1.50 (DP3)
HUB3_SSRX_N: D31.C3, U1.26 (RXN_DS3)
HUB3_SSRX_P: D31.C4, U1.27 (RXP_DS3)
HUB3_SSTX_N: C239.2, D32.C1
HUB3_SSTX_P: C238.2, D32.C2
HUB4_DM: D30.C1, D30.C2, U1.52 (DM4), U1.53 (DP4)
HUB4_SSRX_N: D31.C1, U1.32 (RXN_DS4)
HUB4_SSRX_P: D31.C2, U1.33 (RXP_DS4)
HUB4_SSTX_N: C241.2, D32.C3
HUB4_SSTX_P: C240.2, D32.C4
LCD_DATA0: R9.2, U11.63 (VPA0)
LCD_DATA1: R11.2, U11.62 (VPA1)
LCD_DATA2: R12.2, U11.61 (VPA2)
LCD_DATA3: R13.2, U11.60 (VPA3)
LCD_DATA4: R14.2, U11.59 (VPA4)
LCD_DATA5: R15.2, U11.58 (VPA5)
LCD_DATA6: R16.2, U11.57 (VPA6)
LCD_DATA7: R17.2, U11.56 (VPA7)
LCD_DATA8: R18.2, U11.9 (VPB0)
LCD_DATA9: R19.2, U11.8 (VPB1)
LCD_DATA10: R20.2, U11.7 (VPB2)
LCD_DATA11: R21.2, U11.6 (VPB3)
LCD_DATA12: R22.2, U11.3 (VPB4)
LCD_DATA13: R87.2, U11.2 (VPB5)
LCD_DATA14: R88.2, U11.1 (VPB6)
LCD_DATA15: R89.2, U11.64 (VPB7)
LCD_DATA16: R90.2, U11.18 (VPC0)
LCD_DATA17: R91.2, U11.17 (VPC1)
LCD_DATA18: R92.2, U11.16 (VPC2)
LCD_DATA19: R93.2, U11.15 (VPC3)
LCD_DATA20: R94.2, U11.13 (VPC4)
LCD_DATA21: R108.2, U11.12 (VPC5)
LCD_DATA22: R109.2, U11.11 (VPC6)
LCD_DATA23: R10.2, U11.10 (VPC7)
LCD_DE: R6.2, U11.20 (DE/VREF)
LCD_HSYNC: R8.2, U11.22 (HSYNC/VREF)
LCD_PCLK: R5.2, U11.4 (PCLK)
LCD_VSYNC: R7.2, U11.21 (VSYNC/VREF)
LDO_3V3: C222.2, R117.1, R118.1, R252.1, U14.9 (LDOA1)
unnamed: ANT1.1, C213.1, L3.2
unnamed: C11.1, C12.1, C13.1, C14.1, C15.1, C23.1, FB4.2, U1.10 (VP12_1), U1.16 (VP12_2), U1.22 (VP12_3), U1.28 (VP12_4), U1.34 (VP12_5)
unnamed: C24.1, U1.13 (TXP_DS1)
unnamed: C43.2, R57.2, U5.46 (XI), X6.3
unnamed: C45.2, R57.1, U5.45 (XO), X6.1
unnamed: C46.1, R116.2, X2.1
unnamed: C47.1, J6.5 (CT1), J6.6 (CT2), R61.2
unnamed: C185.1, U1.12 (TXN_DS1)
unnamed: C186.1, U1.19 (TXP_DS2)
unnamed: C197.2, D7.1 (K), R99.1
unnamed: C213.2, C226.1, R133.1
unnamed: C223.1, R122.2, X3.1
unnamed: C232.1, L2.2, U12.23 (VIN_LDO)
unnamed: C236.1, R155.1, X4.1
unnamed: C237.1, U1.18 (TXN_DS2)
unnamed: C238.1, U1.25 (TXP_DS3)
unnamed: C239.1, U1.24 (TXN_DS3)
unnamed: C240.1, U1.31 (TXP_DS4)
unnamed: C241.1, U1.30 (TXN_DS4)
unnamed: C242.2, U1.7 (TXP_UP)
unnamed: C243.2, U1.6 (TXN_UP)
unnamed: C244.2, U1.9 (RXP_UP)
unnamed: C245.2, U1.8 (RXN_UP)
unnamed: C246.2, R143.1, U1.3 (X1), X1.1
unnamed: C247.2, R143.2, U1.4 (X2), X1.3
unnamed: C277.1, R63.2
unnamed: C277.2, Q6.5, U14.4 (SW2)
unnamed: C302.2, R261.2, R264.1, U13.3 (FB)
unnamed: C305.2, U14.53 (VREF)
unnamed: C306.2, U14.56 (LDO5P0)
unnamed: C307.2, U14.54 (LDO3P3)
unnamed: C309.2, R269.1
unnamed: C310.2, R271.1
unnamed: C311.2, R265.2, R270.1
unnamed: C312.2, D1.2 (A2), J3.5, R267.2
unnamed: C313.2, R266.2, R272.1
unnamed: C314.2, D2.2 (A2), J3.3, R268.2
unnamed: D6.2 (A), J14.2
unnamed: D27.A1, J4.3 (DP0)
unnamed: D27.A2, J4.2 (DN_0)
unnamed: D27.A3, J4.12 (DP1)
unnamed: D27.A4, J4.11 (DN_1)
unnamed: D28.A1, J4.5 (RX_N_0)
unnamed: D28.A2, J4.6 (RX_P_0)
unnamed: D28.A3, J4.14 (RX_N_1)
unnamed: D28.A4, J4.15 (RX_P_1)
unnamed: D29.A1, J4.17 (TX_N_1)
unnamed: D29.A2, J4.18 (TX_P_1)
unnamed: D29.A3, J4.8 (TX_N_0)
unnamed: D29.A4, J4.9 (TX_P_0)
unnamed: D30.A1, J5.3 (DP0)
unnamed: D30.A2, J5.2 (DN_0)
unnamed: D30.A3, J5.12 (DP1)
unnamed: D30.A4, J5.11 (DN_1)
unnamed: D31.A1, J5.5 (RX_N_0)
unnamed: D31.A2, J5.6 (RX_P_0)
unnamed: D31.A3, J5.14 (RX_N_1)
unnamed: D31.A4, J5.15 (RX_P_1)
unnamed: D32.A1, J5.17 (TX_N_1)
unnamed: D32.A2, J5.18 (TX_P_1)
unnamed: D32.A3, J5.8 (TX_N_0)
unnamed: D32.A4, J5.9 (TX_P_0)
unnamed: D35.1 (K), R86.2
unnamed: D4.2 (A2), D35.2 (A), J11.13, U11.30 (CEC)
unnamed: D52.2 (A2), J13.B4 (A9/B4/VBUS), J13.B9 (A4/B9/VBUS), Q8.3 (D), Q9.1
unnamed: D62.1, D62.10, J11.1, U11.45 (TX2+)
unnamed: D62.2, D62.9, J11.3, U11.44 (TX2-)
unnamed: D62.4, D62.7, J11.4, U11.43 (TX1+)
unnamed: D62.5, D62.6, J11.6, U11.42 (TX1-)
unnamed: D63.1, D63.10, J11.7, U11.40 (TX0+)
unnamed: D63.2, D63.9, J11.9, U11.39 (TX0-)
unnamed: D63.4, D63.7, J11.10, U11.38 (TXC+)
unnamed: D63.5, D63.6, J11.12, U11.37 (TXC-)
unnamed: D64.1, D64.10, J11.15, U11.33 (DSCL)
unnamed: D64.2, D64.9, J11.16, R85.2, U11.32 (DSDA)
unnamed: D64.4, D64.7, F2.2, J11.18, R84.1, R85.1
unnamed: D64.5, D64.6, J11.19, R84.2, U11.31 (HPD)
unnamed: D65.2 (A), L6.2, U13.1 (SW)
unnamed: FB6.1, U11.14 (VDDIOA(1.8V)), U11.55 (VDDIOB(1.8V))
unnamed: J6.11 (GRL+), R55.2
unnamed: J6.14 (YEL+), R56.2
unnamed: J8.1, R135.1
unnamed: J10.1 (DATA2), R238.2
unnamed: J10.2 (CS), R1.1, R123.1, R237.2
unnamed: J10.3 (DI), R124.1, R236.2
unnamed: J10.5 (SCLK), R125.1, R235.2
unnamed: J10.7 (DO), R126.1, R234.2
unnamed: J10.8 (DATA1), R134.1, R233.2
unnamed: J10.9 (CDN), R147.1, R232.2
unnamed: J13.A5 (CC1), R248.2
unnamed: J13.B5 (CC2), R249.2
unnamed: L1.1, U14.20 (LX5)
unnamed: L2.1, U12.21 (VIN_LDO_OUT)
unnamed: L4.1, Q7.5
unnamed: L7.1, U14.10 (LX3)
unnamed: L8.1, U14.25 (LX4)
unnamed: LED1.1 (K), Q1.3 (D)
unnamed: LED1.2 (A), R2.1
unnamed: LED2.1 (K), Q3.3 (D)
unnamed: LED2.2 (A), R3.1
unnamed: OSC1.3 (CLK), R114.1
unnamed: Q1.2 (G), R4.2, R159.2
unnamed: Q2.3 (D), R138.1, U2.4 (EN)
unnamed: Q3.2 (G), R100.2, R167.2
unnamed: Q6.1, R254.2
unnamed: Q6.4, R255.2
unnamed: Q7.1, R259.2
unnamed: Q7.4, R260.2
unnamed: R257.2, U14.42 (SW6)
unnamed: Q8.1 (G), Q9.3, R163.2
unnamed: Q9.2, Q9.5, Q9.6, R162.2
unnamed: R5.1, U9.AA3 (FUNC_SHARE070/LCD_CLK)
unnamed: R6.1, U9.AA4 (FUNC_SHARE071/LCD_DE)
unnamed: R7.1, U9.AA1 (FUNC_SHARE072/LCD_VSYNC)
unnamed: R8.1, U9.Y2 (FUNC_SHARE073/LCD_HSYNC)
unnamed: R9.1, U9.AA5 (FUNC_SHARE074/LCD_DATA0)
unnamed: R10.1, U9.AD5 (FUNC_SHARE097/LCD_DATA23)
unnamed: R11.1, U9.AA6 (FUNC_SHARE075/LCD_DATA1)
unnamed: R12.1, U9.AB1 (FUNC_SHARE076/LCD_DATA2)
unnamed: R13.1, U9.AA2 (FUNC_SHARE077/LCD_DATA3)
unnamed: R14.1, U9.AB5 (FUNC_SHARE078/LCD_DATA4)
unnamed: R15.1, U9.AB6 (FUNC_SHARE079/LCD_DATA5)
unnamed: R16.1, U9.AC1 (FUNC_SHARE080/LCD_DATA6)
unnamed: R17.1, U9.AB2 (FUNC_SHARE081/LCD_DATA7)
unnamed: R18.1, U9.AB7 (FUNC_SHARE082/LCD_DATA8)
unnamed: R19.1, U9.AG2 (FUNC_SHARE083/LCD_DATA9)
unnamed: R20.1, U9.AD1 (FUNC_SHARE084/LCD_DATA10)
unnamed: R21.1, U9.AB4 (FUNC_SHARE085/LCD_DATA11)
unnamed: R22.1, U9.AH2 (FUNC_SHARE086/LCD_DATA12)
unnamed: R23.2, U1.1 (RTERM)
unnamed: R24.2, U2.2 (ILIM)
unnamed: R25.1, U1.60 (PSELF)
unnamed: R41.2, U5.24 (GTX_CLK)
unnamed: R42.2, U5.25 (TX_EN)
unnamed: R43.2, U5.19 (TXD0)
unnamed: R44.2, U5.20 (TXD1)
unnamed: R45.2, U5.21 (TXD2)
unnamed: R46.2, U5.22 (TXD3)
unnamed: R47.2, U5.35 (RX_CLK)
unnamed: R48.2, U5.33 (RX_DV)
unnamed: R49.2, U5.32 (RXD0)
unnamed: R50.2, U5.31 (RXD1)
unnamed: R51.2, U5.28 (RXD2)
unnamed: R52.2, U5.27 (RXD3)
unnamed: R53.2, U5.36 (MDC)
unnamed: R54.2, U5.37 (MDIO)
unnamed: R59.1, R98.2
unnamed: R60.2, U5.48 (ISET)
unnamed: R62.2, U7.A5 (ZQ0)
unnamed: R63.1, U14.5 (BOOT2)
unnamed: R71.2, U8.A5 (ZQ0)
unnamed: R72.2, U8.A8 (ZQ1)
unnamed: R73.2, R74.2, R75.2
unnamed: R80.2, U9.E12 (DDR0_CAL)
unnamed: R81.2, U9.AG20 (DDR1_CAL)
unnamed: R82.2, U9.C16 (DDR0_ERR_N)
unnamed: R83.2, U9.AJ20 (DDR1_ERR_N)
unnamed: R87.1, U9.AG3 (FUNC_SHARE087/LCD_DATA13)
unnamed: R88.1, U9.AE1 (FUNC_SHARE088/LCD_DATA14)
unnamed: R89.1, U9.AD2 (FUNC_SHARE089/LCD_DATA15)
unnamed: R90.1, U9.AL3 (FUNC_SHARE090/LCD_DATA16)
unnamed: R91.1, U9.AG4 (FUNC_SHARE091/LCD_DATA17)
unnamed: R92.1, U9.AD3 (FUNC_SHARE092/LCD_DATA18)
unnamed: R93.1, U9.AE2 (FUNC_SHARE093/LCD_DATA19)
unnamed: R94.1, U9.AE4 (FUNC_SHARE094/LCD_DATA20)
unnamed: R101.1, R102.1, U16.1 (CE)
unnamed: R103.2, U16.2 (SO_IO1)
unnamed: R104.2, U16.7 (~HOLD/RESET_~IO3)
unnamed: R105.2, U16.3 (~WP_IO2)
unnamed: R106.1, U16.6 (SCK)
unnamed: R107.2, U16.5 (SI_IO0)
unnamed: R108.1, U9.AH4 (FUNC_SHARE095/LCD_DATA21)
unnamed: R109.1, U9.AD4 (FUNC_SHARE096/LCD_DATA22)
unnamed: R110.2, U9.H4 (FUNC_SHARE025/X2C_TX_DATA22)
unnamed: R111.1, U11.34 (EXT_SWING)
unnamed: R113.2, U9.L1 (FUNC_SHARE026/X2C_TX_DATA23)
unnamed: R119.1, U14.58 (CLK)
unnamed: R121.1, U14.59 (DATA)
unnamed: R133.2, R135.2, U12.2 (WL_BT_ANT)
unnamed: R136.1, U12.29 (NC_2)
unnamed: R139.2, R140.2, U12.12 (WL_REG_ON)
unnamed: R141.2, U12.13 (WL_HOST_WAKE)
unnamed: R145.2, U12.17 (SDIO_DATA_CLK)
unnamed: R146.1, U1.55 (PGANG)
unnamed: R156.2, U9.K1 (FUNC_SHARE027/X2C_TX_DATA24)
unnamed: R157.2, U9.M6 (FUNC_SHARE028/X2C_TX_DATA25)
unnamed: R158.2, U9.M5 (FUNC_SHARE032/X2C_TX_DATA29)
unnamed: R58.2, R164.2, U5.42 (RESET)
unnamed: R165.1, U1.61 (RESETJ)
unnamed: R166.2, U14.27 (GPO3)
unnamed: R184.2, U7.A8 (ZQ1)
unnamed: R254.1, U14.3 (DRVH2)
unnamed: R255.1, U14.7 (DRVL2)
unnamed: R256.1, U14.64 (ILIM2)
unnamed: R257.1, U14.41 (BOOT6)
unnamed: R259.1, U14.43 (DRVH6)
unnamed: R260.1, U14.39 (DRVL6)
unnamed: R262.1, U14.45 (ILIM6)
unnamed: R263.2, U13.4 (~SHDN)
unnamed: R265.1, R269.2
unnamed: R266.1, R271.2
unnamed: R267.1, R270.2
unnamed: R268.1, R272.2
unnamed: U2.5 (GND), U2.7 (PAD)
unnamed: U7.A4 (VDD2_00), U7.A9 (VDD2_1), U7.AB4 (VDD2_22), U7.AB9 (VDD2_23), U7.F5 (VDD2_2), U7.F8 (VDD2_3), U7.H1 (VDD2_4), U7.H5 (VDD2_5), U7.H8 (VDD2_6), U7.H12 (VDD2_7), U7.K1 (VDD2_8), U7.K3 (VDD2_9), U7.K10 (VDD2_10), U7.K12 (VDD2_11), U7.N1 (VDD2_12), U7.N3 (VDD2_13), U7.N10 (VDD2_14), U7.N12 (VDD2_15), U7.R1 (VDD2_16), U7.R5 (VDD2_17), U7.R8 (VDD2_18), U7.R12 (VDD2_19), U7.U5 (VDD2_20), U7.U8 (VDD2_21)
unnamed: U7.AA3 (VDDQ_16), U7.AA5 (VDDQ_17), U7.AA8 (VDDQ_18), U7.AA10 (VDDQ_19), U7.B3 (VDDQ_00), U7.B5 (VDDQ_1), U7.B8 (VDDQ_2), U7.B10 (VDDQ_3), U7.D1 (VDDQ_4), U7.D5 (VDDQ_5), U7.D8 (VDDQ_6), U7.D12 (VDDQ_7), U7.F3 (VDDQ_8), U7.F10 (VDDQ_9), U7.U3 (VDDQ_10), U7.U10 (VDDQ_11), U7.W1 (VDDQ_12), U7.W5 (VDDQ_13), U7.W8 (VDDQ_14), U7.W12 (VDDQ_15)
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
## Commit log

2021-06-27 Add files via upload
    Initial Commit - Fork from my GitLab repository
    https://gitlab.com/aswinvenu/beaglev-kicad.git
2021-06-27 Initial commit to working branch, Cloned from the gitlab repository
2021-06-27 All the auto-generated backup files deleted
2021-06-28 Display and camera connector footprint updated
